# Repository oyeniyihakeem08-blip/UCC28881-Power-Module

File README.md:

# UCC28881 High-Voltage Buck Converter Project

## Overview
Design of a single in line UCC28881-based power supply.  
## Contents
| Folder | Description |
|---------|--------------|
| `/symbols` | Custom KiCad symbol library |
| `/footprints` | Custom footprints (.pretty folder) |
| `/simulation` | SPICE models, testbench, waveforms |
| `/fabrication/gerbers` | Gerber & drill files for fabrication |
| `/fabrication/bom` | Bill of materials with manufacturer data |
## How to Open
1. Clone the repo:  
   ```bash
   https://github.com/oyeniyihakeem08-blip/UCC28881-Power-Module.git

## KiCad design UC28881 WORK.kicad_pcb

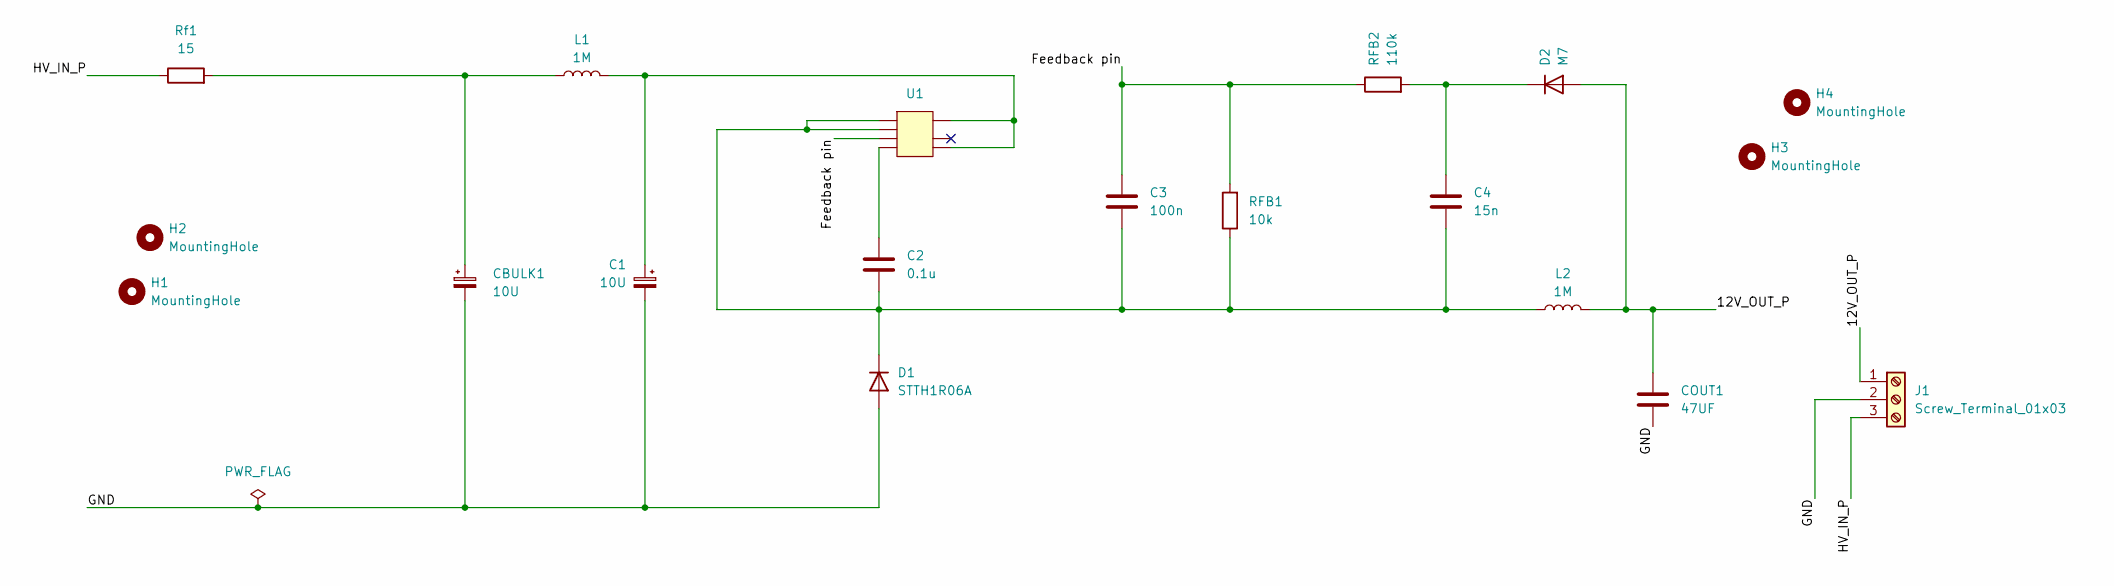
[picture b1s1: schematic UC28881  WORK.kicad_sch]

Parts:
C1: 10U; CP_Radial_D10.0mm_P5.00mm; MANUFACTURER PART NO 106CKS450MLU
C2: 0.1u; C_1206_3216Metric; MANUFACTURER PART NO 12065C104JAT2A
C3: 100n; C_1206_3216Metric; MANUFACTURER PART NO UMF325B7104KNHT
C4: 15n; C_1206_3216Metric; MANUFACTURER PART NO C1206C153K5RACTU
CBULK1: 10U; CP_Radial_D10.0mm_P5.00mm; MANUFACTURER PART NO 106CKS450MLU
COUT1: 47UF; C_1206_3216Metric_Pad1.33x1.80mm_HandSolder; MANUFACTURER PART NO C3216X5R1C476M160AB
D1: STTH1R06A; SMA_STM-M; MANUFACTURER PART NO STTH1R06A
D2: M7; D2; MANUFACTURER PART NO M7
H1, H2, H3, H4: MountingHole; MountingHole_3.2mm_M3_DIN965
J1: Screw_Terminal_01x03; TerminalBlock_Phoenix_MKDS-1,5-3-5.08_1x03_P5.08mm_Horizont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; MANUFACTURER PART NO .
L1: 1M; L_Wurth_WE-PD2HV-7850; MANUFACTURER PART NO 76877530
L2: 1M; DR127; MANUFACTURER PART NO DR127-102-R
RFB1: 10k; RESC3116X65N; MANUFACTURER PART NO CR2010-FX-1002ELF
RFB2: 110k; RESC3216X75N; MANUFACTURER PART NO CR1206-JW-114ELF
Rf1: 15; RF1 RC1206N_PAN-M; MANUFACTURER PART NO ERJ-P08J150V
U1: UCC28881; TI_SOIC-8_D_UCC28881_1.27mm; MANUFACTURER PART NO UCC28810D

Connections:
/12V_OUT_P: COUT1.1, D2.2 (A), J1.1, L2.2
/Feedback pin: C3.1, RFB1.2, RFB2.1, U1.3 (FB)
/GND: C1.2, CBULK1.2, COUT1.2, D1.2 (A), J1.2
/HV_IN_P: J1.3, Rf1.1
unnamed: CBULK1.1, L1.1, Rf1.2
unnamed: C2.2, C3.2, C4.2, D1.1 (K), L2.1, RFB1.1, U1.1 (GND), U1.2 (GND)
unnamed: C4.1, D2.1 (K), RFB2.2
unnamed: C1.1, L1.2, U1.5 (HVIN), U1.8 (DRAIN)
unnamed: C2.1, U1.4 (VDD)

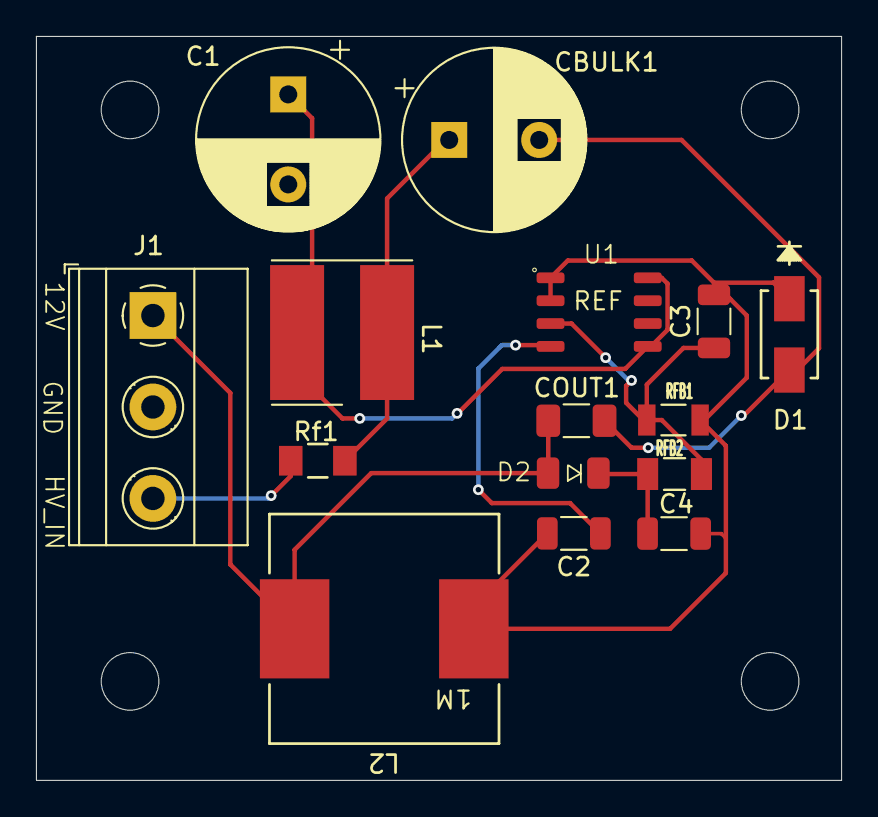
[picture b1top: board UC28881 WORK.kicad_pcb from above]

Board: 2 copper layers, 44.7 x 41.3 mm, 19 parts (0 on the bottom side), 9 nets.

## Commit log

2025-10-08 Initial commit: UCC28881 power supply KiCad project
2025-10-08 Save local work before pull
2025-10-08 Add .gitignore file
2025-10-08 Move .gitignore to project root
2025-10-08 Apply .gitignore globally and remove tracked autosaves
2025-10-09 Updated schematic and fixed silkscreen overlap
2025-10-09 Added footprint
2025-10-10 Removed KiCad backup files
2025-10-10 chore: ignore KiCad backup/cache/lock files
2025-10-10 Save current work before cleaning ignored files
2025-10-10 WIP: checkpoint before cleaning tracked temp files
2025-10-10 Stop tracking KiCad cache, backup, autosave and lock files (kept locally)
2025-10-13 Updated schematic and added RS485 protection circuit
2025-10-16 Updated KiCad project and schematic files
2025-10-24 Updated PCB
2025-10-29 Updated project files and fixed latest edits
2025-10-31 edited pcb layout
2025-10-31 ADDED BOM
